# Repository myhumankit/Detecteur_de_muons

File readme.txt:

This project is an evolution of "CosmicWatch-Desktop-Muon-Detector" published by MIT.
see project description on . 
http://www.cosmicwatch.lns.mit.edu/detector#cosmicwatch

here, the aim was to develop a version of the sensor to support a participatory science program, 
so that it could be taken on board a sailing boat during high-latitude measurement campaigns. 

This new version, developed by My Human Kit , has made it possible to produce and significantly improve the architecture of the sensor 
and its code:
- Evolution of the code so that it can both record data and display it on an OLED screen (whereas MIT proposed 2 different versions of the code). 
- Addition of a GNSS receiver to synchronize data and autonomously record the boat's position 
- Addition of a RTC module to retain date and time in the event of a power cut 
- Improved data display on screen
- Optimization of the detection algo 
- Creation of a python script for data analysis (not yet finished)

my human kit, in carrying out this project, has supported the Astrolabe Expéditions association as part of the "cosmic sail" program.

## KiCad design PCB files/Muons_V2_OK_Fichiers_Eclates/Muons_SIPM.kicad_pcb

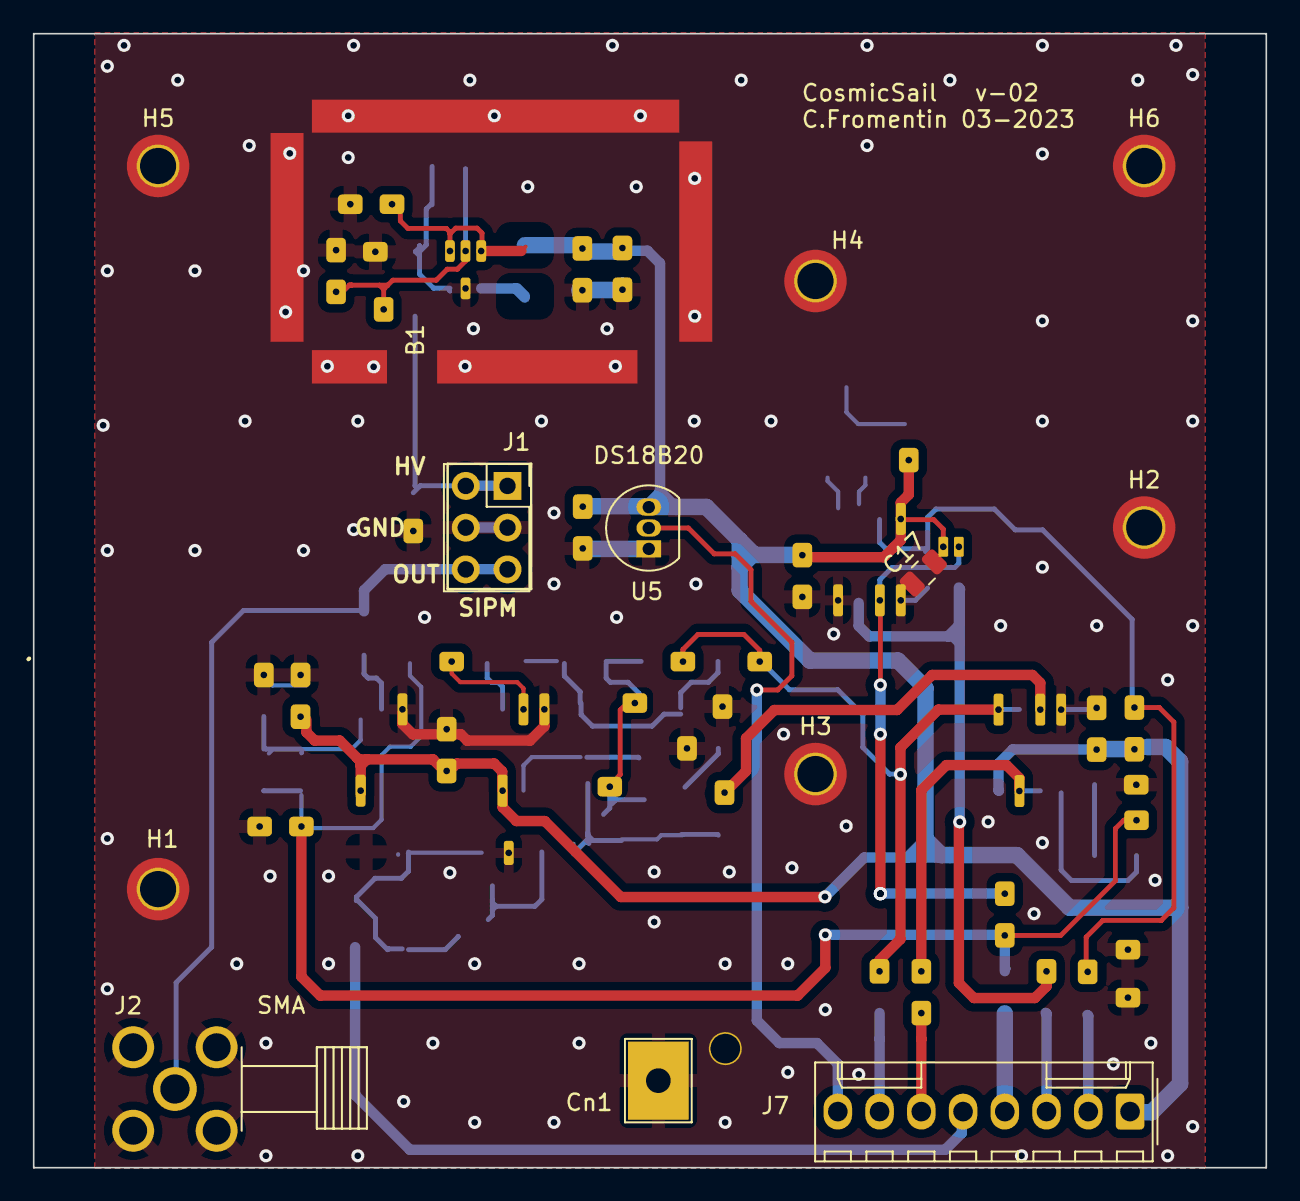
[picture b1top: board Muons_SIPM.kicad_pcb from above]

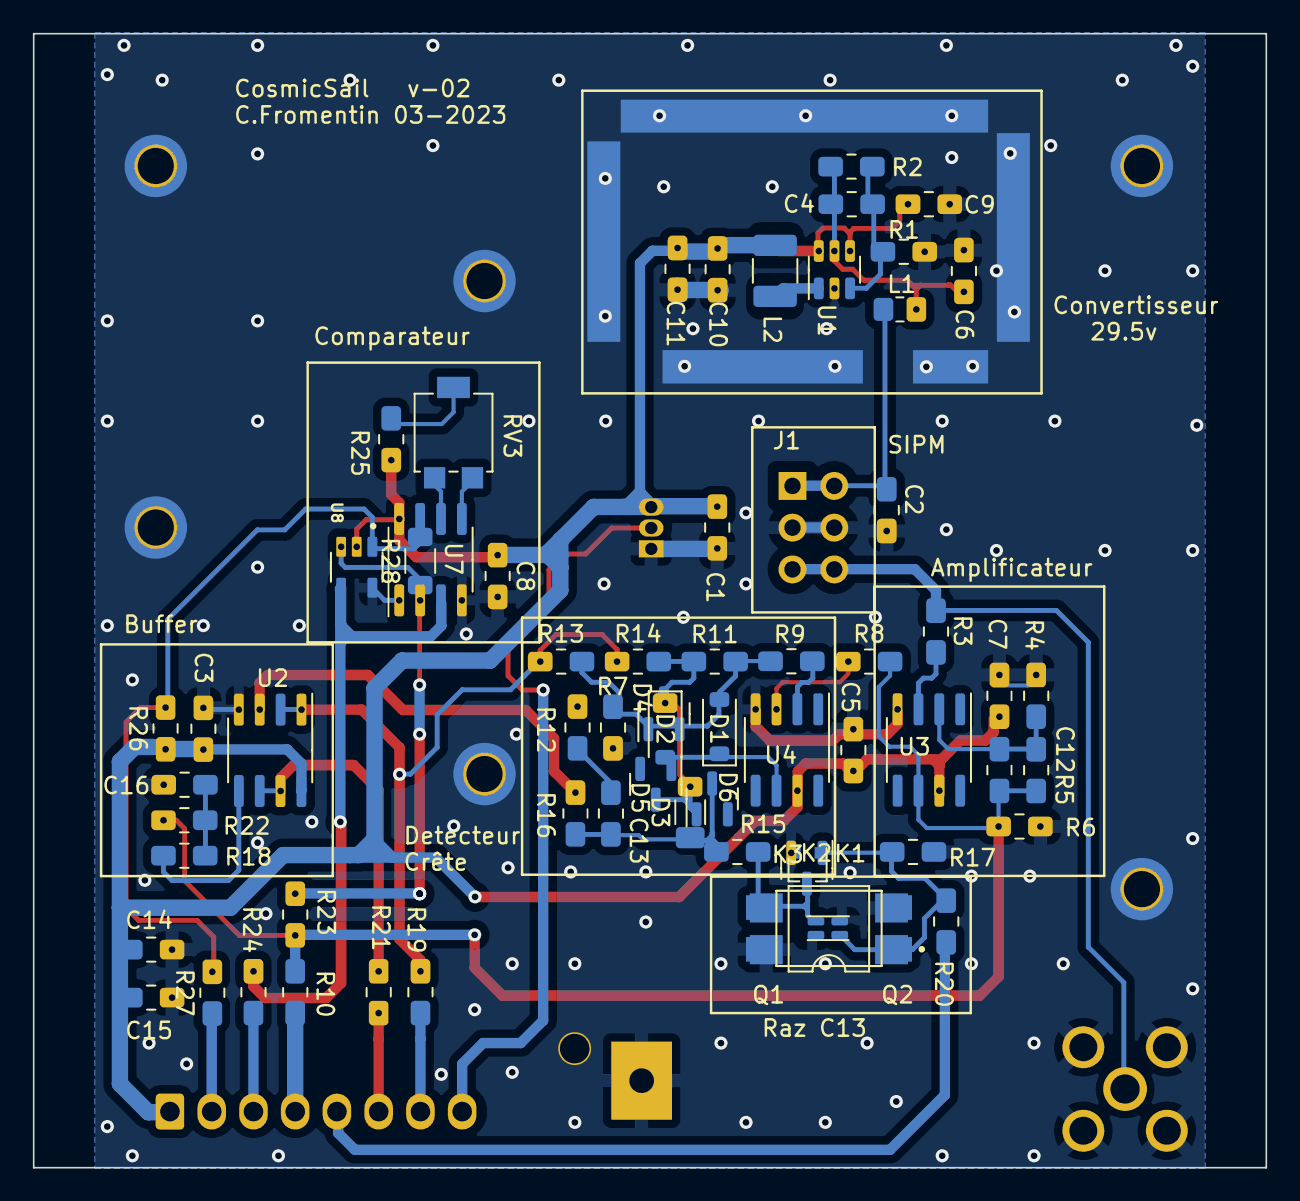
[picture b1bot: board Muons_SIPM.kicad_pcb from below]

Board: 2 copper layers, 75.0 x 69.0 mm, 77 parts (64 on the bottom side), 37 nets.

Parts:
B1: Blindage; Blindage_29.5
C1, C3, C5, C7, C8, C11, C14: 0.1µF; C_0805_Muons
C2, C9: 1µF; C_0805_Muons
C4: 22pF; C_0805_Muons
C6: 0.47µF; C_0805_Muons
C10, C15: 10µF; C_0805_Muons
C12: 10pF; C_0805_Muons
C13: 4.7nF; C_0805_Muons
C16: 100nF; C_0805_Muons
C17: C_0805_2012Metric
Cn1: GND; TestPoint_THTPad_4.75x3.7mm_Drill1.5mm
D1, D2: D_Schottky; D_SOD-123
D3: D_Schottky; R_1206_3216Metric_Pad1.30x1.75mm_HandSolder
D4, D5, D6: MDB301; SOT-23
H1, H2: SiMP; MountingHole_2.2mm_M2_DIN965_Pad_TopBottom
H3, H4, H5, H6: Board_SiMP; MountingHole_2.2mm_M2_DIN965_Pad_TopBottom
J1: WM17457-ND; PinSocket_2x03_P2.54mm_Vertical
J2: 221790-1; TE_221790-1
J7: Conn_01x08_Socket; Molex_KK-254_AE-6410-08A_1x08_P2.54mm_Vertical
K1: G3VM-21GR1
K2: G3VM-41DY; RELAY_G3VM-41DY
K3: G3VM-81UR
L1: Ferrite Bead; R_0805_2012Metric_Pad1.20x1.40mm_HandSolder
L2: 47µH; R_1210_3225Metric_Pad1.30x2.65mm_HandSolder
Q1: BMBT3904; SOT-323_SC-70
Q2: BSS138; SOT-23
R1, R6, R13, R14, R16, R17, R18: 10k; R_0805_Muons
R2: 226k; R_0805_Muons
R3, R4, R8, R9, R12, R15, R23, R24, R26: 1k; R_0805_Muons
R5: 7.5k; R_0805_Muons
R7, R22: 100k; R_0805_Muons
R10, R19, R20, R21, R27: 470; R_0805_Muons
R11: 4.7M; R_0805_Muons
R25: 3.3k; R_0805_Muons
R28: R_1206_3216Metric
RV3: 5k; Potentiometer_Bourns_3314G_Vertical
U1: LT3461; TSOT-23-6
U2: AD823A; SOIC-8_3.9x4.9mm_P1.27mm
U3, U4: LT1806; SOIC-8_3.9x4.9mm_P1.27mm
U5: DS18B20; TO-92_Inline
U7: LM311; SOIC-8_3.9x4.9mm_P1.27mm
U8: MAX988EUK+; SOT95P280X145-5N

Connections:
/S_5V: C1.1, C3.1, C5.1, C7.1, C8.1, C9.1, C10.1, C11.1, C14.1, C15.1, J7.1, L2.2, R25.1, R26.1, U1.4 (CTRL), U1.6 (VIN), U2.8 (V+), U3.7 (V+), U4.7 (V+), U5.3 (V_{DD}), U7.8 (V+), U8.2 (VCC)
/S_COMPAR: J7.2, R27.1
/S_OUT Dac_Filtre: J7.3, R24.2
/S_Out Amp: J7.4, R10.2
/S_Out Amp Filtre: J7.6, R21.1
/S_Out Detect: J7.7, R19.1
/S_Out T° DS18: J7.8, U5.2 (DQ)
/S_RAZ Condo: J7.5, R20.1
GND: B1.1 (GND), C1.2, C2.2, C3.2, C5.2, C6.2, C7.2, C8.2, C9.2, C10.2, C11.2, C14.2, C15.2, C16.2, Cn1.1, H1.1, H2.1, H3.1, H4.1, H5.1, H6.1, J1.3, J1.4, J2.2, J2.3, J2.4, J2.5, K1.2, K1.4, K2.2, K2.4, K3.2, K3.4, Q1.2 (E), Q2.2 (S), R1.1, R4.1, R6.1, R7.1, R12.1, R17.2, U1.2 (GND), U2.4 (V-), U3.4 (V-), U4.4 (V-), U5.1 (GND), U7.1 (GND), U7.4 (V-), U8.5 (VEE)
unnamed: C12.2, R5.2, R6.2, R8.2, R10.1, R22.2, R23.2, U3.6
unnamed: C13.2, R12.2
unnamed: C16.1, R18.2, R22.1
unnamed: D1.2 (A), D4.1 (A), R7.2, R9.2, R11.1, R13.2
unnamed: D1.1 (K), D2.2 (A), D4.3 (K), D5.1 (A), U4.6
unnamed: D2.1 (K), D3.2 (A), D5.3 (K), D6.1 (A), R11.2, R14.2
unnamed: C13.1, D3.1 (K), D6.3 (K), R15.2, R16.2
unnamed: C2.1, J1.1, J1.2, L1.1
unnamed: J1.5, J1.6, J2.1, R3.1
unnamed: K1.1, K2.1, K3.1, Q1.1 (B), Q2.1 (G), R17.1, R20.2
unnamed: K1.3, K2.3, K3.3, Q1.3 (C), Q2.3 (D), R15.1
unnamed: R25.2, RV3.2
unnamed: C4.1, R1.2, R2.1, U1.3 (FB)
unnamed: L2.1, U1.1 (SW)
unnamed: C4.2, C6.1, L1.2, R2.2, U1.5 (VOUT)
unnamed: R16.1, U2.3 (+)
unnamed: R13.1, R14.1, R19.2, U2.1, U2.2 (-)
unnamed: R18.1, U2.5 (+)
unnamed: R21.2, U2.6 (-), U2.7
unnamed: R3.2, U3.3 (+)
unnamed: C12.1, R4.2, R5.1, U3.2 (-)
unnamed: R8.1, U4.3 (+)
unnamed: R9.1, U4.2 (-)
unnamed: R23.1, U7.2 (+), U8.3 (IN+)
unnamed: R24.1, U7.3 (-), U8.4 (IN-)
unnamed: RV3.3, U7.5 (BAL)
unnamed: RV3.1, U7.6 (STRB)
unnamed: R26.2, R27.2, U7.7, U8.1 (OUT)
